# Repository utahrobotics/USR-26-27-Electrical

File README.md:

# USR-26-27-Electrical
The repository for Utah Student Robotics' 2026-2027 competition season. Modularity went pretty well for us last year, so we're leaning even more into it this year!

## Folders
As follows are the various folders in this repo and what they are used for.
### Backplane
- The base-board of our entire robot.
- We reuse existing industry-standard 8-bit "ISA" connectors, which are 62-pin slot-connectors that were most famously used as the expansion slot of choice for the first x86-based PCs produced by IBM.
- See [Backplane](Backplane/Backplane.md) for the **slot pinout!**
### Demoboard
- A soldering-demo/trainer PCB meant for electrical team newbies to practice their (micro)-soldering.
- "You WILL learn how to microsolder" - Vincent
- See [Demoboard](Demoboard/Demoboard.md) for a tiny bit more details

<hr><hr>

## Libraries
- These are our KiCAD Symbol and Footprint libraries. Make sure that whatever Symbols and Footprints you use are placed into *these libraries!* We don't want a mess of unsorted library files!
- Make sure to use relative paths! See the table below:

| **Library Type**  | **Path**                                                 |
| ----------------- | -------------------------------------------------------- |
| Schematic symbols | ``${KIPRJMOD}/../Libraries/Symbols/USR-26-27.kicad_sym`` |
| PCB footprints    | ``${KIPRJMOD}/../Libraries/Footprints/USR-26-27.pretty`` |
| Design blocks		| ``${KIPRJMOD}/../Libraries/DesignBlocks/USR-26-27.kicad_blocks``  |
| Component 3D Models | ``${KIPRJMOD}/../Libraries/3DModels``	|

<hr><hr>

## Contributing
- Please make a **branch** if you plan to make a new PCB! This way, we have less risk of merge conflicts happening from people working on different PCBs at the same time!
	- When you're done, open a **pull-request**, assign an electrical lead as a reviewer, and wait for it to be reviewed and approved.
- Add documentation as you go so that we know what is going on!
	- Documentation should be written in the form of **Markdown (.md)** files placed within the project folders.

<hr><hr>

<span style="opacity: 0.25;">what are you doing down here the readme's over</span>

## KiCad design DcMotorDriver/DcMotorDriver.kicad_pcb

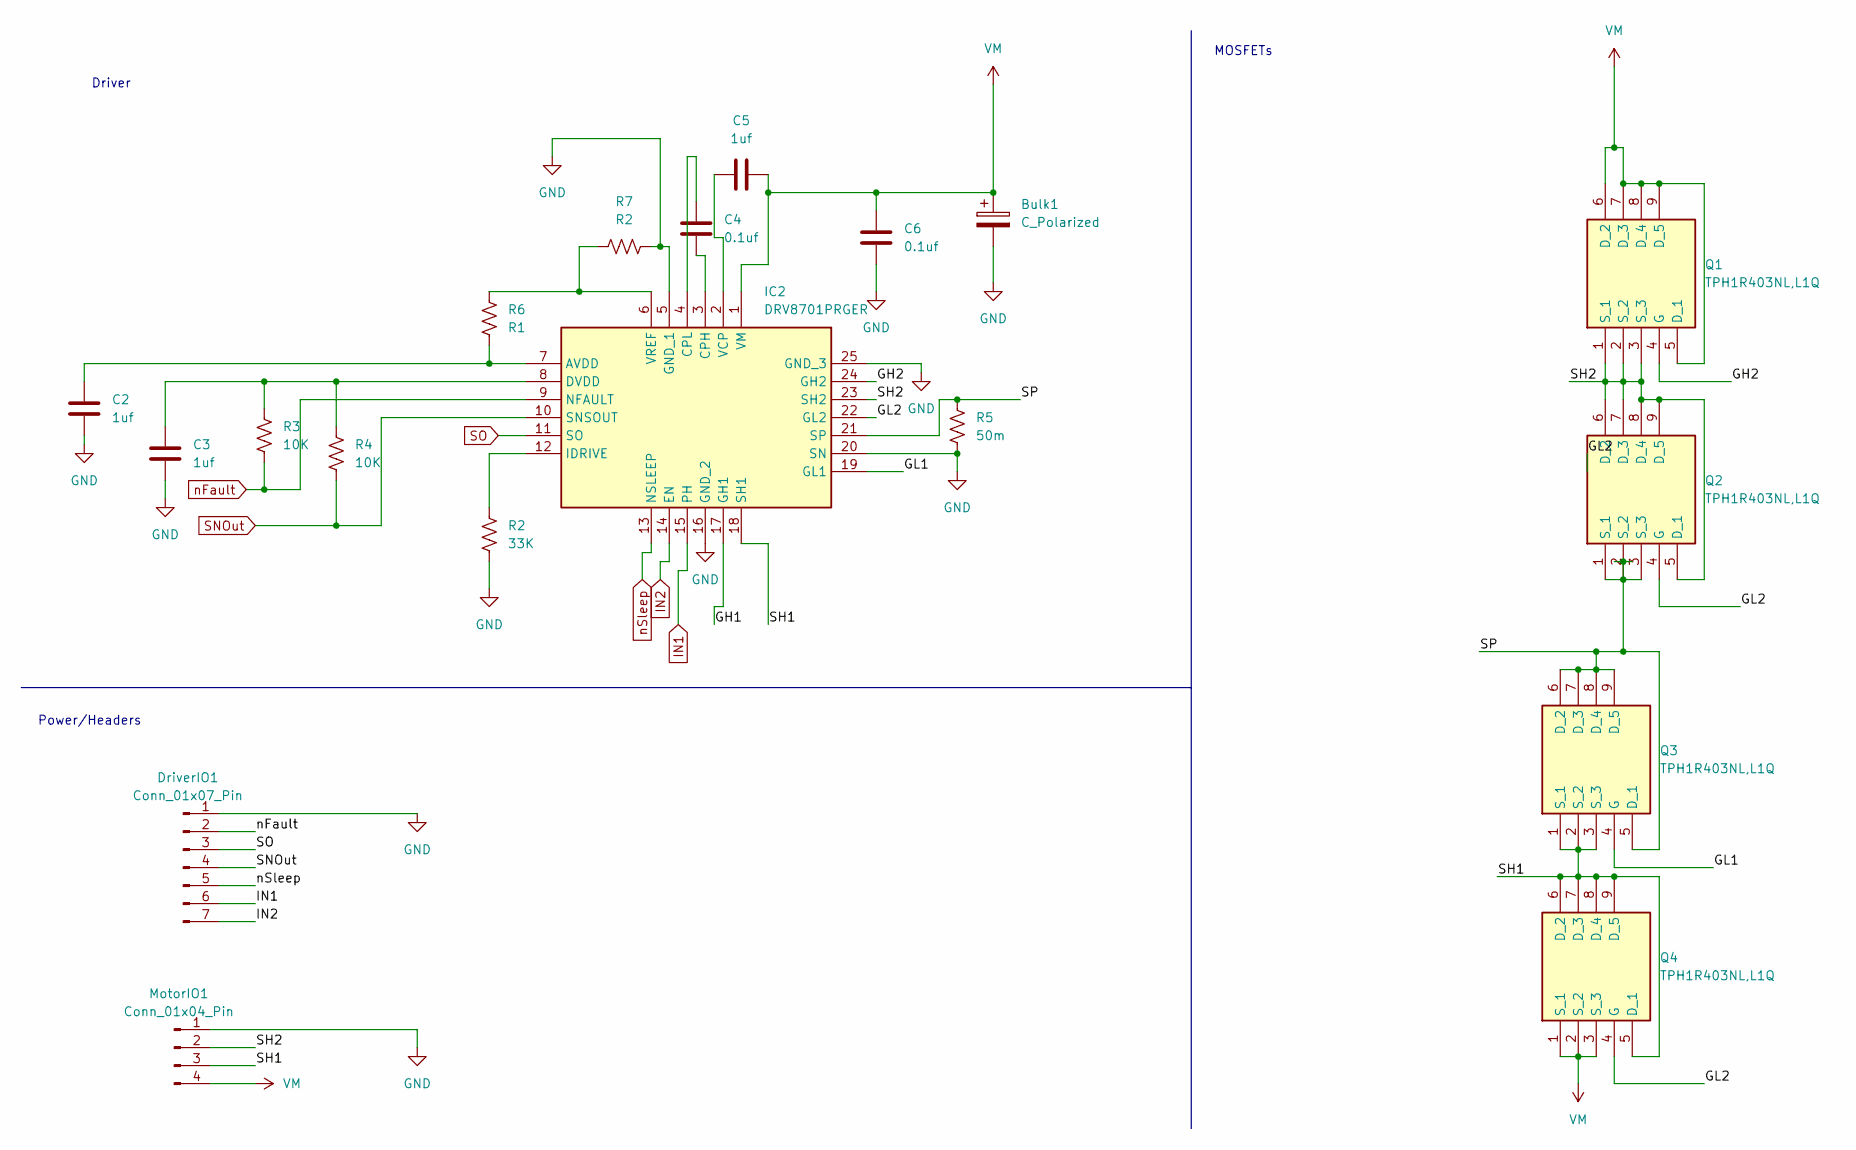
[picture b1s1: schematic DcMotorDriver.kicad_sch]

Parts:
Bulk1: C_Polarized
C2, C3, C5: 1uf; C_0805_2012Metric_Pad1.18x1.45mm_HandSolder
C4, C6: 0.1uf; C_0805_2012Metric_Pad1.18x1.45mm_HandSolder
DriverIO1: Conn_01x07_Pin; TerminalBlock_Xinya_XY308-2.54-7P_1x07_P2.54mm_Horizontal
IC2: DRV8701PRGER; QFN50P400X400X100-25N-D; Manufacturer_Part_Number DRV8701PRGER; Mouser Part Number 595-DRV8701PRGER
MotorIO1: Conn_01x04_Pin; TerminalBlock_MaiXu_MX126-5.0-04P_1x04_P5.00mm
Q1, Q2, Q3, Q4: TPH1R403NL,L1Q; TPH1R403NLL1Q; Manufacturer_Part_Number TPH1R403NL,L1Q; Mouser Part Number 757-TPH1R403NLL1Q
R2: 33K; R_0805_2012Metric_Pad1.20x1.40mm_HandSolder
R3, R4: 10K; R_0805_2012Metric_Pad1.20x1.40mm_HandSolder
R5: 50m; R_0805_2012Metric_Pad1.20x1.40mm_HandSolder
R6: R1; R_0805_2012Metric_Pad1.20x1.40mm_HandSolder
R7: R2; R_0805_2012Metric_Pad1.20x1.40mm_HandSolder

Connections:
/GH1: IC2.17 (GH1)
/GH2: IC2.24 (GH2), Q1.4 (G)
/GL1: IC2.19 (GL1), Q3.4 (G)
/GL2: IC2.22 (GL2), Q2.4 (G), Q4.4 (G)
/SH1: IC2.18 (SH1), MotorIO1.3, Q3.1 (S_1), Q3.2 (S_2), Q3.3 (S_3), Q4.5 (D_1), Q4.6 (D_2), Q4.7 (D_3), Q4.8 (D_4), Q4.9 (D_5)
/SH2: IC2.23 (SH2), MotorIO1.2, Q1.1 (S_1), Q1.2 (S_2), Q1.3 (S_3), Q2.5 (D_1), Q2.6 (D_2), Q2.7 (D_3), Q2.8 (D_4), Q2.9 (D_5)
/SP: IC2.21 (SP), Q2.1 (S_1), Q2.2 (S_2), Q2.3 (S_3), Q3.5 (D_1), Q3.6 (D_2), Q3.7 (D_3), Q3.8 (D_4), Q3.9 (D_5), R5.1
GND: Bulk1.2, C2.2, C3.2, C6.2, DriverIO1.1, IC2.5 (GND_1), IC2.16 (GND_2), IC2.20 (SN), IC2.25 (GND_3), MotorIO1.1, R2.2, R5.2, R7.2
IN1: DriverIO1.6, IC2.15 (PH)
IN2: DriverIO1.7, IC2.14 (EN)
unnamed: C2.1, IC2.7 (AVDD), R6.2
unnamed: C4.2, IC2.3 (CPH)
unnamed: C4.1, IC2.4 (CPL)
unnamed: C3.1, IC2.8 (DVDD), R3.1, R4.1
unnamed: IC2.12 (IDRIVE), R2.1
unnamed: C5.1, IC2.2 (VCP)
unnamed: IC2.6 (VREF), R6.1, R7.1
SNOut: DriverIO1.4, IC2.10 (SNSOUT), R4.2
SO: DriverIO1.3, IC2.11 (SO)
VM: Bulk1.1, C5.2, C6.1, IC2.1 (VM), MotorIO1.4, Q1.5 (D_1), Q1.6 (D_2), Q1.7 (D_3), Q1.8 (D_4), Q1.9 (D_5), Q4.1 (S_1), Q4.2 (S_2), Q4.3 (S_3)
nFault: DriverIO1.2, IC2.9 (NFAULT), R3.2
nSleep: DriverIO1.5, IC2.13 (NSLEEP)

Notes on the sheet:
MOSFETs
Power/Headers
Driver

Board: 2 copper layers, 18 parts (5 on the bottom side), 21 nets, no tracks yet.

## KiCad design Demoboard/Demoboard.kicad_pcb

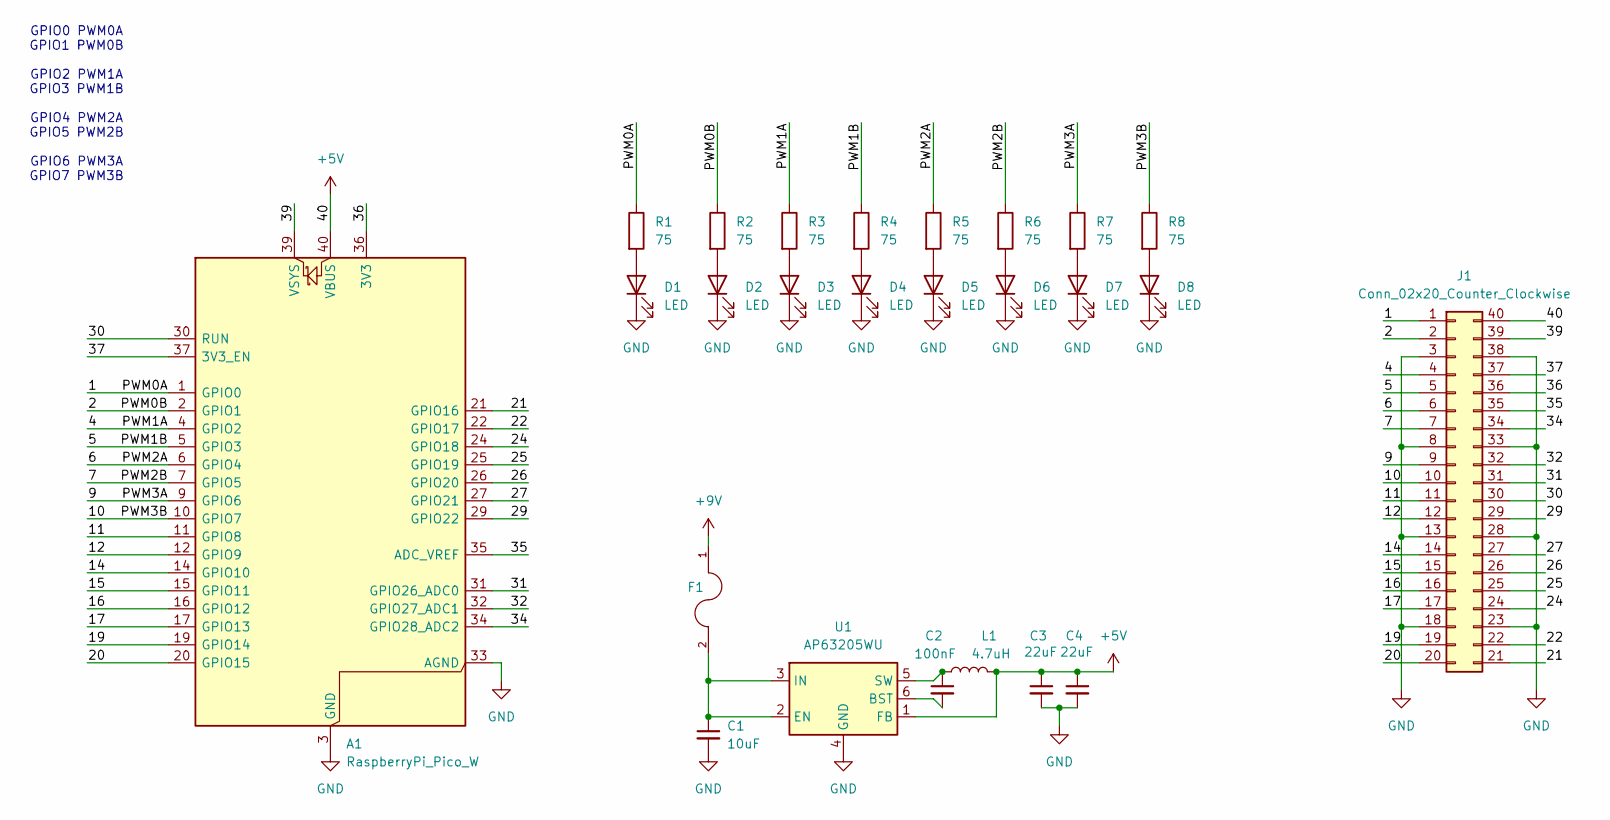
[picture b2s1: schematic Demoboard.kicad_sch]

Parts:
A1: RaspberryPi_Pico_W; RaspberryPi_Pico_Common_Unspecified
C1: 10uF; C_Disc_D7.5mm_W2.5mm_P5.00mm
C2: 100nF; C_Disc_D7.5mm_W2.5mm_P5.00mm
C3, C4: 22uF; C_Disc_D7.5mm_W2.5mm_P5.00mm
D1, D2: LED; LED_D3.0mm
D3, D4: LED; LED_1206_3216Metric_Pad1.42x1.75mm_HandSolder
D5, D6: LED; LED_0805_2012Metric_Pad1.15x1.40mm_HandSolder
D7: LED; LED_0603_1608Metric_Pad1.05x0.95mm_HandSolder
D8: LED; LED_0402_1005Metric_Pad0.77x0.64mm_HandSolder
F1: Fuse Holder: 30A; FUSE_HOLDER_3557-15; PARTREV D
J1: Conn_02x20_Counter_Clockwise; PinSocket_2x20_P2.54mm_Vertical_DIPOrdered
L1: 4.7uH; L_Axial_L11.0mm_D4.5mm_P5.08mm_Vertical_Fastron_MECC
R1, R2: 75; R_Axial_DIN0204_L3.6mm_D1.6mm_P7.62mm_Horizontal
R3, R4: 75; R_1206_3216Metric_Pad1.30x1.75mm_HandSolder
R5, R6: 75; R_0805_2012Metric_Pad1.20x1.40mm_HandSolder
R7: 75; R_0603_1608Metric_Pad0.98x0.95mm_HandSolder
R8: 75; R_0402_1005Metric_Pad0.72x0.64mm_HandSolder
U1: AP63205WU; TSOT-23-6

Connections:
+5V: A1.40 (VBUS), C3.1, C4.1, J1.40, L1.2, U1.1 (FB)
+9V: F1.1; also elsewhere on the board
/1: A1.1 (GPIO0), J1.1, R1.1
/2: A1.2 (GPIO1), J1.2, R2.1
/4: A1.4 (GPIO2), J1.4, R3.1
/5: A1.5 (GPIO3), J1.5, R4.1
/6: A1.6 (GPIO4), J1.6, R5.1
/7: A1.7 (GPIO5), J1.7, R6.1
/9: A1.9 (GPIO6), J1.9, R7.1
/10: A1.10 (GPIO7), J1.10, R8.1
/11: A1.11 (GPIO8), J1.11
/12: A1.12 (GPIO9), J1.12
/14: A1.14 (GPIO10), J1.14
/15: A1.15 (GPIO11), J1.15
/16: A1.16 (GPIO12), J1.16
/17: A1.17 (GPIO13), J1.17
/19: A1.19 (GPIO14), J1.19
/20: A1.20 (GPIO15), J1.20
/21: A1.21 (GPIO16), J1.21
/22: A1.22 (GPIO17), J1.22
/24: A1.24 (GPIO18), J1.24
/25: A1.25 (GPIO19), J1.25
/26: A1.26 (GPIO20), J1.26
/27: A1.27 (GPIO21), J1.27
/29: A1.29 (GPIO22), J1.29
/30: A1.30 (RUN), J1.30
/31: A1.31 (GPIO26_ADC0), J1.31
/32: A1.32 (GPIO27_ADC1), J1.32
/34: A1.34 (GPIO28_ADC2), J1.34
/35: A1.35 (ADC_VREF), J1.35
/36: A1.36 (3V3), J1.36
/37: A1.37 (3V3_EN), J1.37
/39: A1.39 (VSYS), J1.39
GND: A1.3 (GND), A1.8 (GND), A1.13 (GND), A1.18 (GND), A1.23 (GND), A1.28 (GND), A1.33 (AGND), A1.38 (GND), C1.2, C3.2, C4.2, D1.1 (K), D2.1 (K), D3.1 (K), D4.1 (K), D5.1 (K), D6.1 (K), D7.1 (K), D8.1 (K), J1.3, J1.8, J1.13, J1.18, J1.23, J1.28, J1.33, J1.38, U1.4 (GND); also elsewhere on the board
unnamed: D1.2 (A), R1.2
unnamed: D2.2 (A), R2.2
unnamed: D3.2 (A), R3.2
unnamed: D4.2 (A), R4.2
unnamed: D5.2 (A), R5.2
unnamed: D6.2 (A), R6.2
unnamed: D7.2 (A), R7.2
unnamed: D8.2 (A), R8.2
unnamed 42: C1.1, F1.2, U1.2 (EN), U1.3 (IN); also elsewhere on the board
unnamed: C2.2, U1.6 (BST)
unnamed: C2.1, L1.1, U1.5 (SW)

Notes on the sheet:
GPIO0 PWM0A GPIO1 PWM0B GPIO2 PWM1A GPIO3 PWM1B GPIO4 PWM2A GPIO5 PWM2B GPIO6 PWM3A GPIO7 PWM3B

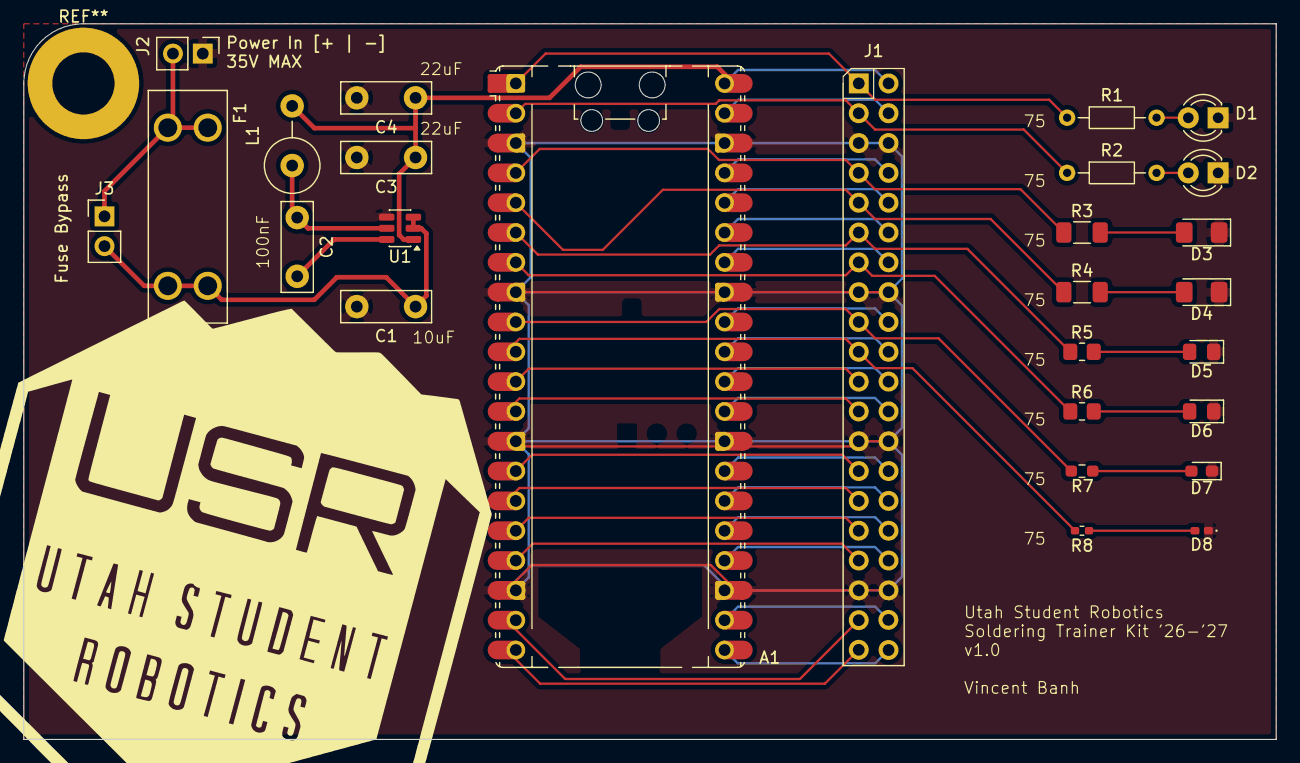
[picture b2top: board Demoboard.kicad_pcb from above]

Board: 2 copper layers, 106.7 x 61.0 mm, 27 parts (0 on the bottom side), 45 nets.

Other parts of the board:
J2, J3: Conn_01x02_Pin; PinHeader_1x02_P2.54mm_Vertical

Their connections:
+9V: J2.2, J3.1; also elsewhere on the board
GND: J2.1; also elsewhere on the board
unnamed 42: J3.2; also elsewhere on the board

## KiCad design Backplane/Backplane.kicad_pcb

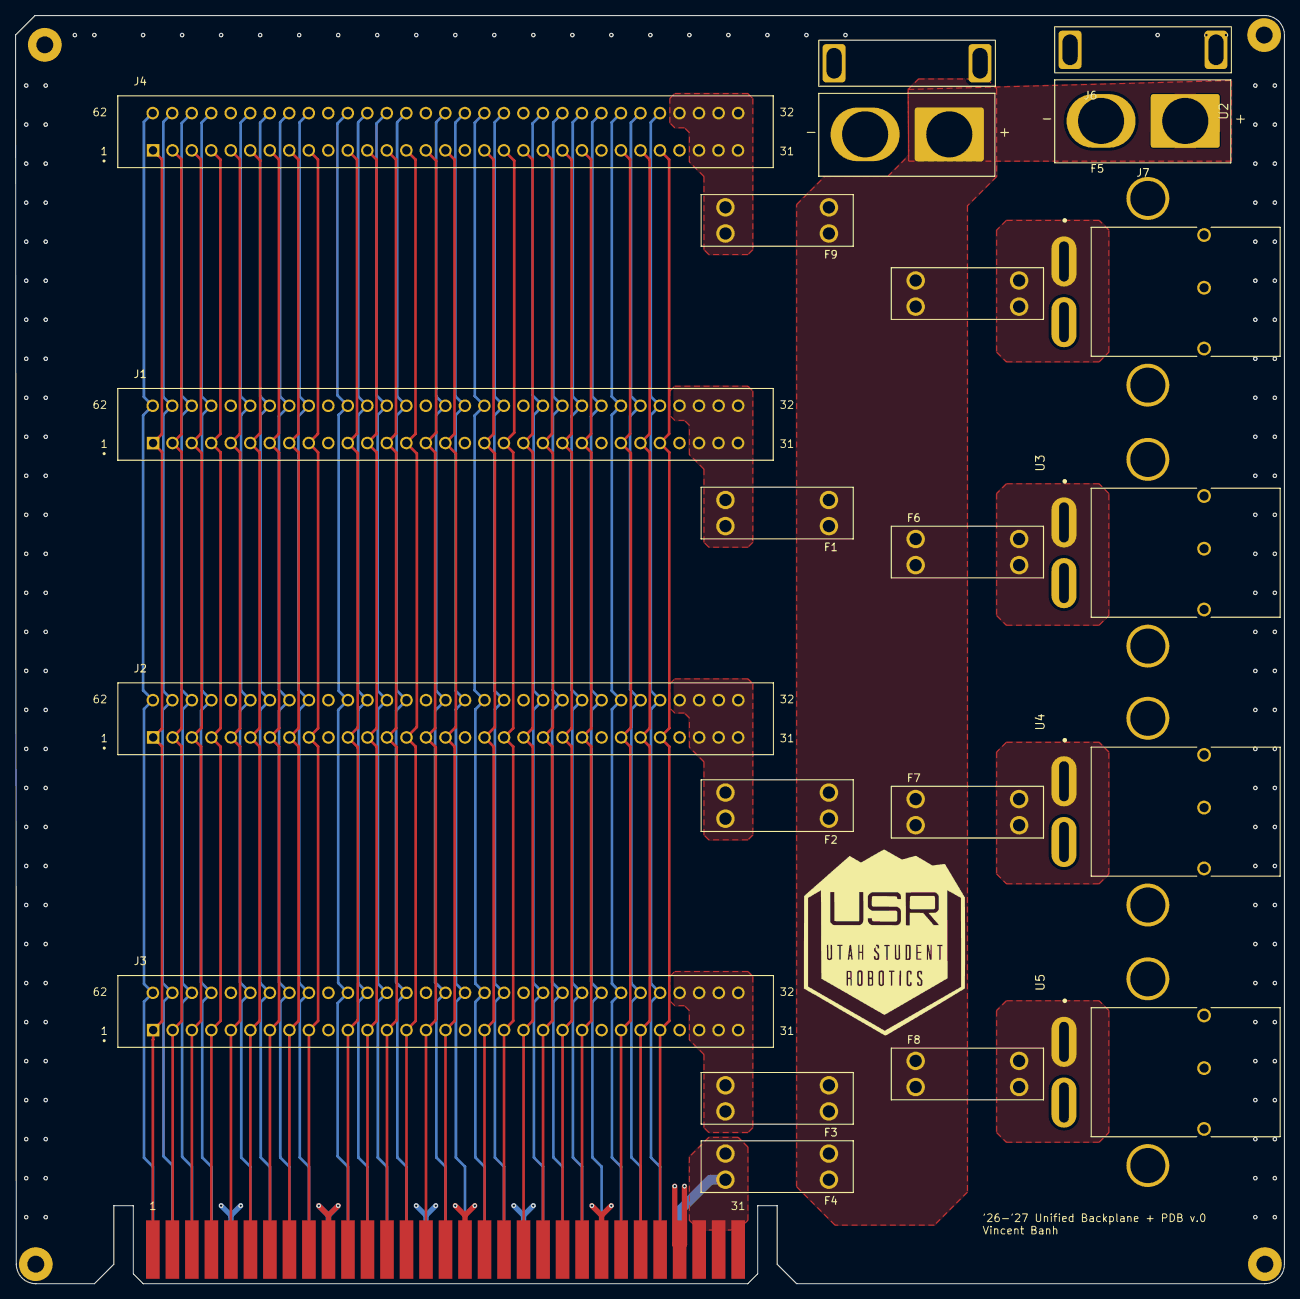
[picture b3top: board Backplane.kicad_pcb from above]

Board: 4 copper layers, 165.2 x 165.1 mm, 20 parts (0 on the bottom side), 58 nets.

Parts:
F1, F2, F3, F4, F5, F6, F7, F8, F9: Fuse Holder: 30A; FUSE_HOLDER_3557-15
J1, J2, J3, J4: USR-62P-BP-SLOT
J5: USR-62P-BP-EDGE
J6, J7: XT90PW-M; AMASS_XT90PW-M_VERTICAL
U2, U3, U4, U5: Anderson PP45 Horiz. 2x1; APP_ASMPR45-1X2-RK

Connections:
+24V: F1.1, F2.1, F3.1, F4.1, F5.1, F6.1, F7.1, F8.1, F9.1, J6.P (POS), J7.P (POS)
/A0: J1.57 (ANALOG-0), J2.57 (ANALOG-0), J3.57 (ANALOG-0), J4.57 (ANALOG-0), J5.57 (ANALOG-0)
/A1: J1.56 (ANALOG-1), J2.56 (ANALOG-1), J3.56 (ANALOG-1), J4.56 (ANALOG-1), J5.56 (ANALOG-1)
/A2: J1.55 (ANALOG-2), J2.55 (ANALOG-2), J3.55 (ANALOG-2), J4.55 (ANALOG-2), J5.55 (ANALOG-2)
/A3: J1.54 (ANALOG-3), J2.54 (ANALOG-3), J3.54 (ANALOG-3), J4.54 (ANALOG-3), J5.54 (ANALOG-3)
/A4: J1.52 (ANALOG-4), J2.52 (ANALOG-4), J3.52 (ANALOG-4), J4.52 (ANALOG-4), J5.52 (ANALOG-4)
/A5: J1.51 (ANALOG-5), J2.51 (ANALOG-5), J3.51 (ANALOG-5), J4.51 (ANALOG-5), J5.51 (ANALOG-5)
/A6: J1.50 (ANALOG-6), J2.50 (ANALOG-6), J3.50 (ANALOG-6), J4.50 (ANALOG-6), J5.50 (ANALOG-6)
/A7: J1.49 (ANALOG-7), J2.49 (ANALOG-7), J3.49 (ANALOG-7), J4.49 (ANALOG-7), J5.49 (ANALOG-7)
/A8: J1.47 (ANALOG-8), J2.47 (ANALOG-8), J3.47 (ANALOG-8), J4.47 (ANALOG-8), J5.47 (ANALOG-8)
/A9: J1.46 (ANALOG-9), J2.46 (ANALOG-9), J3.46 (ANALOG-9), J4.46 (ANALOG-9), J5.46 (ANALOG-9)
/A10: J1.45 (ANALOG-10), J2.45 (ANALOG-10), J3.45 (ANALOG-10), J4.45 (ANALOG-10), J5.45 (ANALOG-10)
/A11: J1.44 (ANALOG-11), J2.44 (ANALOG-11), J3.44 (ANALOG-11), J4.44 (ANALOG-11), J5.44 (ANALOG-11)
/A12: J1.42 (ANALOG-12), J2.42 (ANALOG-12), J3.42 (ANALOG-12), J4.42 (ANALOG-12), J5.42 (ANALOG-12)
/A13: J1.41 (ANALOG-13), J2.41 (ANALOG-13), J3.41 (ANALOG-13), J4.41 (ANALOG-13), J5.41 (ANALOG-13)
/A14: J1.40 (ANALOG-14), J2.40 (ANALOG-14), J3.40 (ANALOG-14), J4.40 (ANALOG-14), J5.40 (ANALOG-14)
/A15: J1.39 (ANALOG-15), J2.39 (ANALOG-15), J3.39 (ANALOG-15), J4.39 (ANALOG-15), J5.39 (ANALOG-15)
/D0: J1.4 (DIGITAL-0), J2.4 (DIGITAL-0), J3.4 (DIGITAL-0), J4.4 (DIGITAL-0), J5.4 (DIGITAL-0)
/D1: J1.5 (DIGITAL-1), J2.5 (DIGITAL-1), J3.5 (DIGITAL-1), J4.5 (DIGITAL-1), J5.5 (DIGITAL-1)
/D2: J1.6 (DIGITAL-2), J2.6 (DIGITAL-2), J3.6 (DIGITAL-2), J4.6 (DIGITAL-2), J5.6 (DIGITAL-2)
/D3: J1.7 (DIGITAL-3), J2.7 (DIGITAL-3), J3.7 (DIGITAL-3), J4.7 (DIGITAL-3), J5.7 (DIGITAL-3)
/D4: J1.8 (DIGITAL-4), J2.8 (DIGITAL-4), J3.8 (DIGITAL-4), J4.8 (DIGITAL-4), J5.8 (DIGITAL-4)
/D5: J1.9 (DIGITAL-5), J2.9 (DIGITAL-5), J3.9 (DIGITAL-5), J4.9 (DIGITAL-5), J5.9 (DIGITAL-5)
/D6: J1.11 (DIGITAL-6), J2.11 (DIGITAL-6), J3.11 (DIGITAL-6), J4.11 (DIGITAL-6), J5.11 (DIGITAL-6)
/D7: J1.12 (DIGITAL-7), J2.12 (DIGITAL-7), J3.12 (DIGITAL-7), J4.12 (DIGITAL-7), J5.12 (DIGITAL-7)
/D8: J1.13 (DIGITAL-8), J2.13 (DIGITAL-8), J3.13 (DIGITAL-8), J4.13 (DIGITAL-8), J5.13 (DIGITAL-8)
/D9: J1.14 (DIGITAL-9), J2.14 (DIGITAL-9), J3.14 (DIGITAL-9), J4.14 (DIGITAL-9), J5.14 (DIGITAL-9)
/D10: J1.15 (DIGITAL-10), J2.15 (DIGITAL-10), J3.15 (DIGITAL-10), J4.15 (DIGITAL-10), J5.15 (DIGITAL-10)
/D11: J1.16 (DIGITAL-11), J2.16 (DIGITAL-11), J3.16 (DIGITAL-11), J4.16 (DIGITAL-11), J5.16 (DIGITAL-11)
/D12: J1.18 (DIGITAL-12), J2.18 (DIGITAL-12), J3.18 (DIGITAL-12), J4.18 (DIGITAL-12), J5.18 (DIGITAL-12)
/D13: J1.19 (DIGITAL-13), J2.19 (DIGITAL-13), J3.19 (DIGITAL-13), J4.19 (DIGITAL-13), J5.19 (DIGITAL-13)
/D14: J1.20 (DIGITAL-14), J2.20 (DIGITAL-14), J3.20 (DIGITAL-14), J4.20 (DIGITAL-14), J5.20 (DIGITAL-14)
/D15: J1.21 (DIGITAL-15), J2.21 (DIGITAL-15), J3.21 (DIGITAL-15), J4.21 (DIGITAL-15), J5.21 (DIGITAL-15)
/D16: J1.22 (DIGITAL-16), J2.22 (DIGITAL-16), J3.22 (DIGITAL-16), J4.22 (DIGITAL-16), J5.22 (DIGITAL-16)
/D17: J1.23 (DIGITAL-17), J2.23 (DIGITAL-17), J3.23 (DIGITAL-17), J4.23 (DIGITAL-17), J5.23 (DIGITAL-17)
/D18: J1.25 (DIGITAL-18), J2.25 (DIGITAL-18), J3.25 (DIGITAL-18), J4.25 (DIGITAL-18), J5.25 (DIGITAL-18)
/D19: J1.26 (DIGITAL-19), J2.26 (DIGITAL-19), J3.26 (DIGITAL-19), J4.26 (DIGITAL-19), J5.26 (DIGITAL-19)
/D20: J1.27 (DIGITAL-20), J2.27 (DIGITAL-20), J3.27 (DIGITAL-20), J4.27 (DIGITAL-20), J5.27 (DIGITAL-20)
/D21: J1.36 (DIGITAL-21), J2.36 (DIGITAL-21), J3.36 (DIGITAL-21), J4.36 (DIGITAL-21), J5.36 (DIGITAL-21)
/D22: J1.37 (DIGITAL-22), J2.37 (DIGITAL-22), J3.37 (DIGITAL-22), J4.37 (DIGITAL-22), J5.37 (DIGITAL-22)
/D23: J1.38 (DIGITAL-23), J2.38 (DIGITAL-23), J3.38 (DIGITAL-23), J4.38 (DIGITAL-23), J5.38 (DIGITAL-23)
/I2C-SCLK: J1.1 (I2C-SCLK), J2.1 (I2C-SCLK), J3.1 (I2C-SCLK), J4.1 (I2C-SCLK), J5.1 (I2C-SCLK)
/I2C-SDA: J1.2 (I2C-SDA), J2.2 (I2C-SDA), J3.2 (I2C-SDA), J4.2 (I2C-SDA), J5.2 (I2C-SDA)
/SPI-A0: J1.61 (SPI-A0), J2.61 (SPI-A0), J3.61 (SPI-A0), J4.61 (SPI-A0), J5.61 (SPI-A0)
/SPI-A1: J1.60 (SPI-A1), J2.60 (SPI-A1), J3.60 (SPI-A1), J4.60 (SPI-A1), J5.60 (SPI-A1)
/SPI-A2: J1.59 (SPI-A2), J2.59 (SPI-A2), J3.59 (SPI-A2), J4.59 (SPI-A2), J5.59 (SPI-A2)
/SPI-MISO: J1.3 (SPI-MISO), J2.3 (SPI-MISO), J3.3 (SPI-MISO), J4.3 (SPI-MISO), J5.3 (SPI-MISO)
/~SPI-CSEL: J1.62 (~SPI-CSEL), J2.62 (~SPI-CSEL), J3.62 (~SPI-CSEL), J4.62 (~SPI-CSEL), J5.62 (~SPI-CSEL)
GND: J1.10 (GND), J1.17 (GND), J1.24 (GND), J1.28 (GND), J1.43 (GND), J1.48 (GND), J1.53 (GND), J1.58 (GND), J2.10 (GND), J2.17 (GND), J2.24 (GND), J2.28 (GND), J2.43 (GND), J2.48 (GND), J2.53 (GND), J2.58 (GND), J3.10 (GND), J3.17 (GND), J3.24 (GND), J3.28 (GND), J3.43 (GND), J3.48 (GND), J3.53 (GND), J3.58 (GND), J4.10 (GND), J4.17 (GND), J4.24 (GND), J4.28 (GND), J4.43 (GND), J4.48 (GND), J4.53 (GND), J4.58 (GND), J5.10 (GND), J5.17 (GND), J5.24 (GND), J5.28 (GND), J5.43 (GND), J5.48 (GND), J5.53 (GND), J5.58 (GND), J6.N (NEG), J7.N (NEG), U2.2 (GND), U3.2 (GND), U4.2 (GND), U5.2 (GND)
unnamed: F1.2, J1.29 (24V), J1.30 (24V), J1.31 (24V), J1.32 (24V), J1.33 (24V), J1.34 (24V), J1.35 (24V)
unnamed: F2.2, J2.29 (24V), J2.30 (24V), J2.31 (24V), J2.32 (24V), J2.33 (24V), J2.34 (24V), J2.35 (24V)
unnamed: F3.2, J3.29 (24V), J3.30 (24V), J3.31 (24V), J3.32 (24V), J3.33 (24V), J3.34 (24V), J3.35 (24V)
unnamed: F4.2, J5.29 (24V), J5.30 (24V), J5.31 (24V), J5.32 (24V), J5.33 (24V), J5.34 (24V), J5.35 (24V)
unnamed: F9.2, J4.29 (24V), J4.30 (24V), J4.31 (24V), J4.32 (24V), J4.33 (24V), J4.34 (24V), J4.35 (24V)
unnamed: F5.2, U2.1 (VCC)
unnamed: F6.2, U3.1 (VCC)
unnamed: F7.2, U4.1 (VCC)
unnamed: F8.2, U5.1 (VCC)
